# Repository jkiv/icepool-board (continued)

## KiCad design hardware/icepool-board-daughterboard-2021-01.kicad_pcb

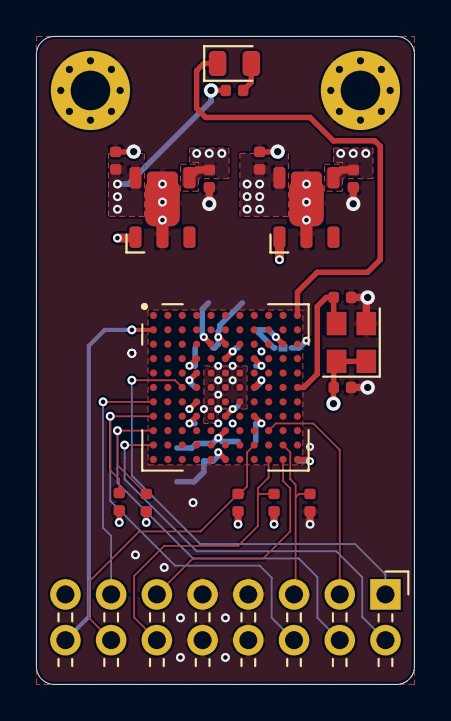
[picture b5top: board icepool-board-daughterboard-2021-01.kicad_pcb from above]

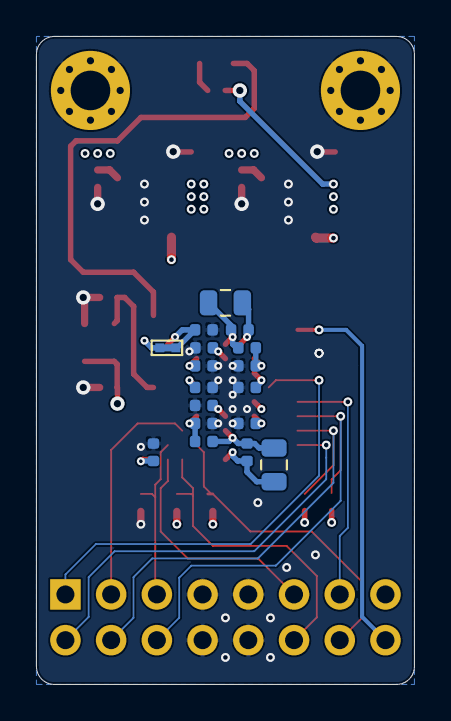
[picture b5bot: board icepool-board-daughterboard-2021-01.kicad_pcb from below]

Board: 4 copper layers, 21.0 x 36.0 mm, 37 parts (17 on the bottom side), 23 nets.

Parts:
C16, C23, C24, C25, C26, C27, C28, C29, C30, C32, C33, C34, C36: 0.1u; C_0402_1005Metric
C17: DNP; C_0402_1005Metric
C19, C20, C21, C22: 4.7u; C_0402_1005Metric
C31, C35: 10u; C_0805_2012Metric
D2: LED_IND; LED_0805_2012Metric
H5, H6: MountingHole_Pad; MountingHole_2.2mm_M2_Pad_Via
J5: Conn_02x08_Odd_Even; PinHeader_2x08_P2.54mm_Horizontal
JP1: CUT_2V5; SolderJumper-2_P1.3mm_Bridged_Pad1.0x1.5mm
R14: 1k; R_0402_1005Metric
R15, R16: 100R; R_0402_1005Metric
R17, R18, R19, R20, R31: 10k; R_0402_1005Metric
U6, U7: AP7361C_SOT-89-5; SOT89-5
U8: iCE40HX8K-BG121(121-Ball_caBGA); BGA-121_11x11_9.0x9.0mm
X2: ASEM1-12.000MHZ; Oscillator_SMD_Abracon_ASE-4Pin_3.2x2.5mm

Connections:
+1V2: C22.1, C24.2, C27.2, C29.2, C33.2, R15.2, R16.2, U7.5, U8.D4, U8.D8, U8.H4, U8.H8
+3V3: C16.2, C20.1, C23.2, C25.2, C28.2, C30.2, C34.2, JP1.1, R14.2, R18.1, R19.1, R20.1, R31.1, U6.5, U7.1, U8.D6, U8.E4, U8.F8, U8.G4, U8.H6, U8.L11, X2.1, X2.4
+5V: C19.1, C21.1, J5.15, U6.1, U6.4, U7.4
/ice40hx8k-daughter-board/CDONE: J5.14, R20.2, U8.K8
/ice40hx8k-daughter-board/CLK_FPGA: C17.2, U8.F11, X2.3
/ice40hx8k-daughter-board/CRESET_B: J5.12, R18.2, U8.L9
/ice40hx8k-daughter-board/READY: J5.16, U8.B1
/ice40hx8k-daughter-board/SCK0: J5.11, U8.L10
/ice40hx8k-daughter-board/SCK1: J5.13, U8.G1
/ice40hx8k-daughter-board/SDI0: J5.3, U8.J9
/ice40hx8k-daughter-board/SDI1: J5.1, U8.F3
/ice40hx8k-daughter-board/SDO1: J5.2, U8.K1
/ice40hx8k-daughter-board/ice40-hx8k-bg121/GNDPLL0: C31.2, C32.2, U8.L6
/ice40hx8k-daughter-board/ice40-hx8k-bg121/GNDPLL1: C35.2, C36.2, U8.C5
/ice40hx8k-daughter-board/ice40-hx8k-bg121/VCCPLL0: C31.1, C32.1, R15.1, U8.J6
/ice40hx8k-daughter-board/ice40-hx8k-bg121/VCCPLL1: C35.1, C36.1, R16.1, U8.C6
/ice40hx8k-daughter-board/ice40-hx8k-bg121/VPP_2V5: C26.2, JP1.2, U8.C10
/ice40hx8k-daughter-board/~CS0: J5.5, R17.2, U8.K10
/ice40hx8k-daughter-board/~CS1: J5.6, R31.2, U8.H1
/ice40hx8k-daughter-board/~LED: D2.1, U8.A11
/ice40hx8k-daughter-board/~RW: J5.4, R19.2, U8.J1
GND: C16.1, C17.1, C19.2, C20.2, C21.2, C22.2, C23.1, C24.1, C25.1, C26.1, C27.1, C28.1, C29.1, C30.1, C33.1, C34.1, H5.1, H6.1, J5.7, J5.8, J5.9, J5.10, R17.1, U6.2, U7.2, U8.E5, U8.E6, U8.E7, U8.F5, U8.F6, U8.F7, U8.G5, U8.G6, U8.G7, U8.H5, X2.2
unnamed: D2.2, R14.1

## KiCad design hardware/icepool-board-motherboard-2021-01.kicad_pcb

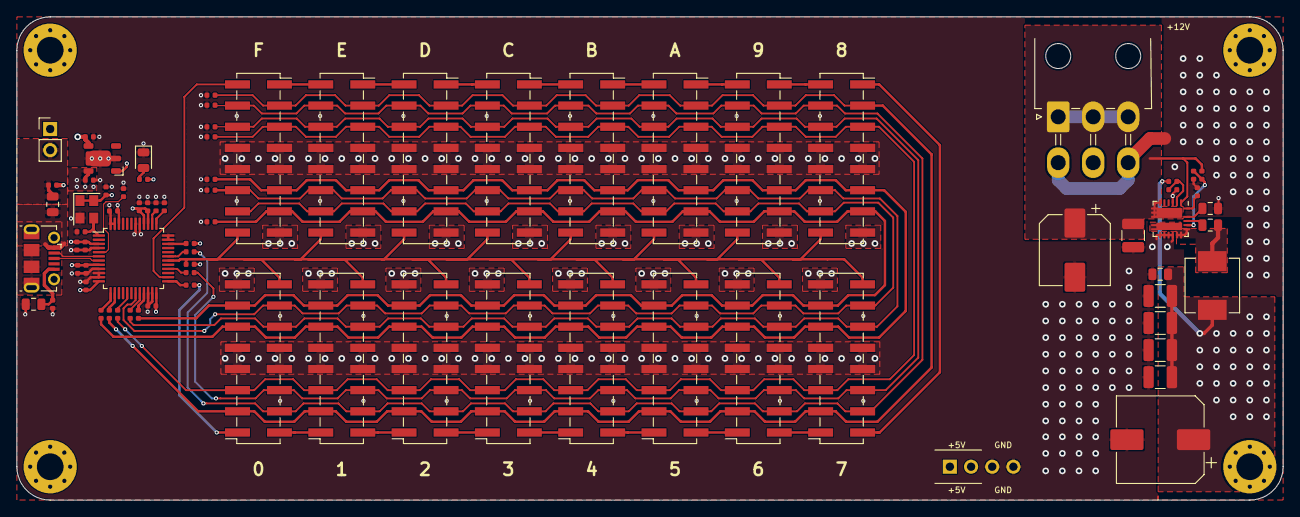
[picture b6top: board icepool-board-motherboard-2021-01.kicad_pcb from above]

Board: 4 copper layers, 152.0 x 58.0 mm, 83 parts (0 on the bottom side), 55 nets.

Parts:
C1, C3, C11, C12: 4.7u; C_0402_1005Metric
C2, C4, C5, C6, C7, C8, C13, C14, C18, C48, C49, C50: 0.1u; C_0402_1005Metric
C9: 0.01u; C_0402_1005Metric
C10: DNP; C_0402_1005Metric
C37: 0.1n; C_0402_1005Metric
C38, C43, C44, C45, C46: 22u; C_1210_3225Metric
C39: 47u; CP_Elec_8x10
C40, C42: 0.1u; C_0805_2012Metric
C41: 4.7u; C_0805_2012Metric
C47: 100u; CP_Elec_10x10
D1: PWRLED; LED_0805_2012Metric
FB1: FB; L_0805_2012Metric
H1, H2, H3, H4: MountingHole_Pad; MountingHole_3.2mm_M3_Pad_Via
J1: USB_B_Micro; USB_Micro-B_Molex-105017-0001
J2: Conn_01x02; PinHeader_1x02_P2.54mm_Vertical
J3: PCIe_6pin; Molex_Mini-Fit_Jr_5569-06A2_2x03_P4.20mm_Horizontal
J4, J6, J7, J8, J9, J10, J11, J12, J13, J14, J15, J16, J17, J18, J19, J20: Conn_02x08_Odd_Even; PinSocket_2x08_P2.54mm_Vertical_SMD
J21: Conn_01x04; PinHeader_1x04_P2.54mm_Vertical
L1: 0.68u; L_Vishay_IHLP-2525
R1: 4k7; R_0402_1005Metric
R2, R3, R4, R5, R7, R8, R11, R13: 22R; R_0402_1005Metric
R6: 4.7k; R_0402_1005Metric
R9: 12k; R_0402_1005Metric
R10, R24, R26, R27, R28, R29, R30: DNP; R_0402_1005Metric
R12: 100k; R_0805_2012Metric
R21: 620k; R_0402_1005Metric
R22: 220k; R_0402_1005Metric
R23: 30k; R_0402_1005Metric
R25: 1k; R_0402_1005Metric
U1: FT232H; LQFP-48_7x7mm_P0.5mm
U2: AP7361C_SOT-89-5; SOT89-5
U9: AOZ2255LQI-30; QFN-22L-EP2_4x4mm_P0.5mm
X1: ASEM1-12.000MHZ; Oscillator_SMD_Abracon_ASE-4Pin_3.2x2.5mm

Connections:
+3V3: C1.1, C2.1, C3.1, C4.1, C8.2, C12.1, C13.1, C14.1, C18.1, C49.1, C50.1, R1.1, R6.2, R25.2, U1.3, U1.8, U1.12, U1.24, U1.39, U1.40, U1.46, U2.5, X1.1, X1.4
+5V: C11.1, C42.1, C43.1, C44.1, C45.1, C46.1, C47.1, J2.1, J4.15, J6.15, J7.15, J8.15, J9.15, J10.15, J11.15, J12.15, J13.15, J14.15, J15.15, J16.15, J17.15, J18.15, J19.15, J20.15, J21.1, J21.2, L1.2, R22.1, U2.1, U2.4
+12V: C38.1, C39.1, J3.1, J3.2, J3.3, R21.1, U9.1, U9.6, U9.7, U9.8, U9.9
/icepool-motherboard/12V-5V Buck/LX: C40.2, L1.1, U9.10, U9.11, U9.16, U9.17, U9.18
/icepool-motherboard/CDONE: J4.14, J6.14, J7.14, J8.14, J9.14, J10.14, J11.14, J12.14, J13.14, J14.14, J15.14, J16.14, J17.14, J18.14, J19.14, J20.14, U1.19
/icepool-motherboard/CIPO1: J20.2, U1.26
/icepool-motherboard/COPI0: J4.3, J6.3, J7.3, J8.3, J9.3, J10.3, J11.3, J12.3, J13.3, J14.3, J15.3, J16.3, J17.3, J18.3, J19.3, J20.3, R3.1, R24.2
/icepool-motherboard/COPI1: J4.1, R8.1
/icepool-motherboard/CRESET_B: J4.12, J6.12, J7.12, J8.12, J9.12, J10.12, J11.12, J12.12, J13.12, J14.12, J15.12, J16.12, J17.12, J18.12, J19.12, J20.12, R5.1, R30.2
/icepool-motherboard/FT_CLK: C10.2, U1.1, X1.3
/icepool-motherboard/FT_RST: R6.1, U1.34
/icepool-motherboard/READY: J4.16, J6.16, J7.16, J8.16, J9.16, J10.16, J11.16, J12.16, J13.16, J14.16, J15.16, J16.16, J17.16, J18.16, J19.16, J20.16, R25.1, U1.30
/icepool-motherboard/SCK0: J4.11, J6.11, J7.11, J8.11, J9.11, J10.11, J11.11, J12.11, J13.11, J14.11, J15.11, J16.11, J17.11, J18.11, J19.11, J20.11, R2.1, R10.2
/icepool-motherboard/SCK1: J4.13, J6.13, J7.13, J8.13, J9.13, J10.13, J11.13, J12.13, J13.13, J14.13, J15.13, J16.13, J17.13, J18.13, J19.13, J20.13, R7.1, R27.2
/icepool-motherboard/SDO1_0: J4.2, J6.1
/icepool-motherboard/SDO1_1: J6.2, J9.1
/icepool-motherboard/SDO1_2: J9.2, J10.1
/icepool-motherboard/SDO1_3: J10.2, J13.1
/icepool-motherboard/SDO1_4: J13.2, J14.1
/icepool-motherboard/SDO1_5: J14.2, J17.1
/icepool-motherboard/SDO1_6: J17.2, J18.1
/icepool-motherboard/SDO1_7: J7.1, J18.2
/icepool-motherboard/SDO1_8: J7.2, J8.1
/icepool-motherboard/SDO1_9: J8.2, J11.1
/icepool-motherboard/SDO1_10: J11.2, J12.1
/icepool-motherboard/SDO1_11: J12.2, J15.1
/icepool-motherboard/SDO1_12: J15.2, J16.1
/icepool-motherboard/SDO1_13: J16.2, J19.1
/icepool-motherboard/SDO1_14: J19.2, J20.1
/icepool-motherboard/USB_D+: J1.3, U1.7
/icepool-motherboard/USB_D-: J1.2, U1.6
/icepool-motherboard/VBUS: C7.1, FB1.1, J2.2
/icepool-motherboard/~CS0: J4.5, J6.5, J7.5, J8.5, J9.5, J10.5, J11.5, J12.5, J13.5, J14.5, J15.5, J16.5, J17.5, J18.5, J19.5, J20.5, R4.1, R26.2
/icepool-motherboard/~CS1: J4.6, J6.6, J7.6, J8.6, J9.6, J10.6, J11.6, J12.6, J13.6, J14.6, J15.6, J16.6, J17.6, J18.6, J19.6, J20.6, R11.1, R28.2
/icepool-motherboard/~RW: J4.4, J6.4, J7.4, J8.4, J9.4, J10.4, J11.4, J12.4, J13.4, J14.4, J15.4, J16.4, J17.4, J18.4, J19.4, J20.4, R13.1, R29.2
GND: C1.2, C2.2, C3.2, C4.2, C5.2, C6.2, C7.2, C8.1, C9.2, C10.1, C11.2, C12.2, C13.2, C14.2, C18.2, C37.2, C38.2, C39.2, C41.2, C42.2, C43.2, C44.2, C45.2, C46.2, C47.2, C48.2, C49.2, C50.2, D1.1, J3.4, J3.6, J4.7, J4.8, J4.9, J4.10, J6.7, J6.8, J6.9, J6.10, J7.7, J7.8, J7.9, J7.10, J8.7, J8.8, J8.9, J8.10, J9.7, J9.8, J9.9, J9.10, J10.7, J10.8, J10.9, J10.10, J11.7, J11.8, J11.9, J11.10, J12.7, J12.8, J12.9, J12.10, J13.7, J13.8, J13.9, J13.10, J14.7, J14.8, J14.9, J14.10, J15.7, J15.8, J15.9, J15.10, J16.7, J16.8, J16.9, J16.10, J17.7, J17.8, J17.9, J17.10, J18.7, J18.8, J18.9, J18.10, J19.7, J19.8, J19.9, J19.10, J20.7, J20.8, J20.9, J20.10, J21.3, J21.4, R9.2, R10.1, R12.1, R23.2, R24.1, R26.1, R27.1, R28.1, R29.1, R30.1, U1.4, U1.9, U1.10, U1.11, U1.22, U1.23, U1.35, U1.36, U1.41, U1.42, U1.47, U1.48, U2.2, U9.3, U9.12, U9.13, U9.14, U9.15, X1.2
unnamed: C5.1, U1.38
unnamed: C6.1, U1.37
unnamed: C9.1, J1.5, R12.2
unnamed: C37.1, R21.2, U9.19
unnamed: C40.1, U9.20
unnamed: C41.1, U9.21
unnamed: C48.1, U9.22
unnamed: D1.2, R1.2
unnamed: FB1.2, J1.1
unnamed: R2.2, U1.13
unnamed: R3.2, U1.14
unnamed: R4.2, U1.17
unnamed: R5.2, U1.20
unnamed: R7.2, U1.21
unnamed: R8.2, U1.25
unnamed: R9.1, U1.5
unnamed: R11.2, U1.28
unnamed: R13.2, U1.31
unnamed: R22.2, R23.1, U9.2

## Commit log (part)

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2018-05-31 Initial commit.
2018-05-31 Fat fingers, twice.
2018-06-29 Shooting for 16x for some reason.
2019-09-03 Moving to "icepool" to generalize project.
2019-09-06 Saving 2018/KiCad 4 design on separate branch for reference.
2019-09-06 Starting over with KiCad 5 and prototyping.
2019-09-06 Created empty project for KiCad 5 version.
2019-09-06 Added 'external' folder for 3rd party libraries.
2019-09-06 Updated README.md.
2019-09-06 Linked Digikey atomic library.
2019-09-06 Starting design. Added icepool-library.
2019-09-06 Updated LICENSE.txt to reflect 2018-KiCad4 branch.
2019-09-06 Added icepool-library. See jkiv/icepool-library repo.
2019-09-07 Beginning to add MCU to schematic.
2019-09-07 Started adding FPGA sheet.
2019-09-07 Much progress.
    Added FPGA, RS485, pullups, test points, etc.
2019-09-09 Most of schematic laid out. Almost ready to route.
2019-09-11 Associated more things with CPL parts.
2019-09-16 Moved ~WE to GBIN4. Added CLK (issue #10).
2019-09-16 Added oscillator module.
    Went with the smaller ASDMB but kept reference to larger
    ASV.
    Since they're small and relatively inexpensive, it might be
    worthwhile to just have one oscillator per FPGA.
    Wrong net name for OSC/CLK.
2019-09-26 Nearing schematic finalization for 2019-00
2019-09-26 Next, RJ45 board-to-board? Or checklists.
2019-09-28 Went through hardware checklist (issue #11).
2019-09-28 Beginning BOM, issue #12.
2019-09-28 Associated all parts, except FPGAs.
2019-09-28 Added icepool-library footprint for 9x9mm BGA ca-121
2019-09-28 Went through DRC. Found some bugs.
2019-09-28 Beginning layout.
    Briefly looked for distribution-type
    screw terminals for PWR, but opting to
    go with JST VR for now.
2019-09-30 Formatted path in README as code.
2019-09-30 Updated README to reflect cloning external libs.
2019-10-01 Playing with layout a bit more.
2019-10-02 Placed FGPA caps and fanout.
    Switched FPGA caps to 0603. May switch everything.
    Next: set up OSC and IO buses.
2019-10-05 Uncommitted layout progress from a while ago...
2019-10-07 More layout work.
2019-10-07 Removed many R0s. Updated layout.
2019-10-07 Layout done-ish. Running traces.
    Comms bus needs some breathing room... Trying at 6mil.
2019-10-07 Reduced READY_ANY/READY_ALL to READY.
2019-10-10 IO bus tracks laid.
2019-10-10 Removed test points. Removing soldermask instead.
2019-10-10 Opting to probe exposed pins. 0.5mm too small.
2019-10-10 Power planes and lines placed.
2019-10-10 Final touches. Ran DRC. Some things need tweaking.
2019-10-11 Took on DRC.
    Two errors remain: two vias within blonde one of 5 mil, probably OK?
2019-10-11 Fixed missing trace on FPGA0.
2019-10-19 Softened corners. Shrunk C29/C42 by 0.1mm for DRC.
2019-10-21 Rethinking things...
2019-10-21 Moderate rework.
    * Added USB.
    * Moved around SERCOMs to accommodate USB.
    * Moved power connector to another edge.
    * Updated FPGA oscillator model/footprint.
2019-10-22 Changed power switch. Removed overhanging silks.
2019-10-22 Updated README for tagging.
2019-10-26 Removing non-empty clone targets.
2019-10-26 Moved icepool-board/ to hardware/
2019-10-29 Many updates, needs re-routing:
    * Added two ICE40HX8K's.
    * Changed ICE40 pinout to make routing more straightforward.
    * Most inputs to ICE40 are now global fabric -- why not?
    * Added CRESET_B to each FPGA, allowing for per-FPGA bitstreams.
    * Replaced LDOs with beefier ones
    * Added second +1.2V rail.
2019-10-30 More work on layout. LDO may not cut it.
2019-11-02 Moved icepool-board/ to hardware/ to match master *shrugs*
2019-11-02 Moving icepool-library into jk-library.
2019-11-02 Nevermind, I'll do it another day.
2019-11-02 Updated setup in README.md
2019-11-02 Change power supplies to FAN2306s (6A buck).
2019-11-02 Updated gitignore for hardware/. Reassociated PCB footprints.
2019-11-03 Added footprints for FAN, etc.
2019-11-06 Power supply. Power supply layout. FPGA passives.
2019-11-07 More passives.
2019-11-11 Removing non-empty hardware/external/ dirs.
2019-11-15 Layout nearly done.
2019-11-15 Isolated shield ground on RJ45s
2019-11-15 Added net for isolated RJ45 shield ground.
2019-11-15 Moved some FSilk items for pretty picture.
2019-11-18 Isolated F copper ground fill on power supplies.
2019-11-25 Finalizing board.
2019-11-25 Generated gerbers. Ordered.
2019-11-26 SWD header is 1.27mm pitch, not 1.00mm (Oops.)
2019-11-26 Generated interactive BOM.
2020-01-11 Moved i2c.
2020-01-11 Updated some passive sizes. Replaced term jumper with handsolder.
2020-01-14 Migrating from icepool-library to jkiv-kicad-library.
2020-01-14 Updated doc references to icepool-library.
2020-01-23 Removed RS485. Removed pull up resistors. Added USB shield filtering.
2020-01-25 Minor rework.
    - Changed 5V regulator for SC70 part.
    - Added RC filter on USB shield-to-ground.
    - Placement of MCU and friends.
    - Removed all external pullup/downs except I2C.
2020-01-26 Added bulk cap for 12V in.
2020-01-28 Reintroduced RS485... not sure yet.
2020-01-28 Nay on RS485 for now. Chosen ISL chip for RS422. May use JST instead of RJ45.
2020-02-02 DRC passes.
2020-02-02 Beefed up some traces.
2020-02-05 Added software control of RS485 transmit.
2020-02-19 Preparations for 2020-01 gerbers.
2020-02-25 Added pullup/limit on reset. SWD Header TH > SMD.
2020-02-25 Updated BOM html
2020-03-02 Added OSHW logo. Ready to order 2020-01.
2020-04-07 Fixed 3v3 and 1v2 buck component values.
2020-04-26 Changed MCU crystal to 2.5x2mm @ 16MHz. Resolves #20
2020-04-26 Moved around RX and TX on MCU. Addresses issue #19.
2020-04-26 Added 2.54mm headers for SWD. Addresses issue #24.
2020-04-26 Added 2.54mm headers for UART. Addresses issue #23.
2020-04-27 Reverted ISL83485 with ISL83488. Addresses issue #22
2020-04-27 Changed CRESET_B_x to SPI_SS_B_x. Common CDONE, CRESET_B.
    Using I2C PAD[2], PAD[3] for CDONE, CRESET_B respectively.
    If not able to use them as GPIO with I2C enabled, we'll abandon I2C.
    Addresses issue #21.
2020-04-28 Fixed 2V5, updated FPGA oscillators, and added indicator LEDs.
    Addresses issues #26, #27, and #28 respectively.
2020-04-28 Starting to re-layout. Removed PWR switch.
2020-04-28 Updated layout. Removed fiducials.
    Completes issues #19, #20, #21, #22, #23, #24, #26, #27, and #28.
2020-04-29 Fixed some label placements.
2020-05-10 Initial firmware commit.
    Code being developed using Atmel Studio, but placed here manually
    to keep it under source control.
    So far,
    - ringbuffer.c works
    - uart.c works
    - main.c changes with what's being developed
2020-05-16 Major net code milestone. Not sure what was added.
    LOL.
2020-05-18 A little too much new code.
2020-05-19 Unifying Atmel Studio project with this repo.
    No more copy/paste.
2020-05-19 Removed /firmware/src/. Now /firmware/icepool-firmware.
2020-05-20 Firmware compiles.
2020-05-20 Updated tests -- passing.
2020-05-20 End of night 2020-05-19
2020-05-26 Beginning interface_termios.c. Wrote echo_simple host test.
2020-05-26 Moving icepool-firmware to src
2020-05-26 asm/termbits.h not needed on RPi.
2020-05-26 Made echo_simple more noisy.
2020-05-26 Just checking serial setup.
2020-05-26 CNEW_RTSCTS not on RPi.
2020-05-26 CRTSCTS definition found on RPi.
2020-05-26 CRTSCTS definition found on RPi -- nevermind.
2020-05-26 Plucking away at bugs?
2020-09-12 Completely reworked schematic. Two FGPAs, LDOs, no SMPS, etc.
2020-09-12 Layed out passives for FGPA. Need to duplicate.
2020-09-21 Layout progress.
2020-09-22 Finished data bus layout.
2020-10-18 Swapped ~WE and SCK for SERCOM1.
    DIPO = 0x3, DOPO = 0x0.
    Fixes issue #34.
2020-10-27 Continuing on rework.
    * Removed 0.05" header -- not needed for this version.
    * Ran DRC -- reworking via sizes and bus as a result.
    * In the midst of reworking VCC plane, access to +3v3.
    * Need to rework data bus.
2020-11-10 Simplified version with LDOs ready. Passes DRC.
    Addresses issue #32.
2020-11-10 Generated BOM and gerbers.
2020-11-10 Fixed line/formatting in schematic.
2020-11-10 [2020-04] Regenerated BOM and gerbers.
2020-11-10 Added 3D render to README.
2020-12-22 Added labels to breakout pins. Rotated button.
2021-01-02 202009 Rework done.
2021-01-04 Progress on mother/daughter boards.
    Note for future: kicad 5.1.4 crashes when deleting "locked" vias.
2021-01-09 Finished up layout. Ordered boards.
2021-02-23 Added HTML BOM for mother and daughter boards.
2021-02-23 Added gerbers used in 2021-01 boards. Fixed USB GND.
    Fixed issue #40.
2021-02-23 Swapped GND and PWR planes.
    Fixes issue #43.
2021-02-23 Fixed a couple more thermal reliefs.
    Addresses issue #41.
2021-02-23 Spread out bus signals more uniformly.
    Addresses issue #44.
2021-02-23 +silkscreen. Version++. +OSHW
    Addresses issue #46.
2021-02-23 Refactored for TPS62133 (5V, 3A) buck converter.
    Changes motherboard dimensions. Changes motherboard stencil.
    Addresses issue #42.
2021-02-23 Added labels for DEF and FSW.
2021-03-02 Replaced FT232H with FT2232H for additional SPI interface (issue #45).
    Moved +1V2 traces on daughterboard from In1 to In2 (issue #43).
    Fixed routing GND, SHIELD on USB (issue #40).
2021-03-06 Added optional EEPROM for FT2232H (issue #47).
    Removed 2021-01 board layout files.
    Shoved motherboard headers for more space.
    Made bus lines narrower (12mil > 9mil).
2021-04-12 Added daisy-chained READY for ready-all support.
    Reconfigured header pinout on motherboard and ice40hx8k daughter board.
    Addresses issue #48.
2021-04-12 Replaced +5V rail with +3v3 using drop-in replacement buck.
    Removed most +5V fills. +5V still available via VBUS.
    Addresses issue #49.
2021-04-21 Updated 3D models and README.
    Re-introduced M2 screw holes for daughter board.
    Also includes changes to KiCAD schematics and layout. Not sure
    exactly what changed since last commit.
2021-04-21 Updated README to use relative path for images.
2021-04-21 Trying to make images smaller in README.
    github does not honor style="zoom: ..."
2021-04-21 Fixed typo in README.
2021-05-02 Removed icepool-power.pro
2021-06-07 Updated README.
2021-06-08 Added external dependencies as submodules.
2021-06-08 Final tweaks for 2021-02.
    * Shrunk daughter board PCB.
    * Added ~READY[15] pulldown resistor and jumper.
    * Removed GND edge connection.
    * Added ~READY pin header.
    * Reworked daughter board signals.
2021-06-08 Updated README for submodules and 2021-02 graphics.
2021-06-08 Added 2021-02 gerbers and boms.
2021-07-21 Removed icepool-power.pro -- not a separate project.
2021-08-10 Added Kedarius/RPi-CM4-Kicad as a dependency.
2021-08-14 Push for streaming.
2021-08-15 More progress on CM4 blade motherboard.
    - Utilizing 40-pin 2mm "stamp" form factor.
2021-08-18 Progress on schematic.
    - GPIO selected for FPGAs.
    - Added 1Wire temperature sensors. (Optional)
    - Added UART. (Not sure if needed.)
    - And other stuff.
2021-08-18 Moved node_array.sch to node-array.sch for consistency.
2021-08-20 Commit to move to Desktop to continue work.
    - Not sure about PoE if it involves flyback design. Modularize?
    - 12V from USB PD using STUSB4500 or similar, or high current 5V?
    - Not sure how to set up 12V USB PD from Pi on which it relies.
2021-08-20 Progress on PoE -- using TPS23731.
    - Circuit design is a bit complex. Not sure if ideal.
    - Can fall back on MP8007, LTC4267, and possibly LT4267.
2021-08-20 Updated submodule jkiv-kicad-library
2021-08-21 Moved motherboards and daughterboards to different project folders.
    - Added USB PD chip.
    - Removed PoE and will become daughterboard.
    - Beginning basic layout.
2021-08-27 Commit prior to stream.
2021-08-29 Start of week commit.
2021-09-10 Prestream commit.
2021-09-12 Post-stream commit.
    * Vertical daughterboards to reduce board size and complexity.
    * Flip-flopping on design choices, but meh.
2022-02-12 New basis for icepool daughterboard.
2022-02-13 Yet another rework in progress.
2022-02-21 Added forgotten 'node-array.sch'
2022-02-22 (Re-?)Added node.sch.
2022-07-05 SODIMM re-design + KiCad 6.
